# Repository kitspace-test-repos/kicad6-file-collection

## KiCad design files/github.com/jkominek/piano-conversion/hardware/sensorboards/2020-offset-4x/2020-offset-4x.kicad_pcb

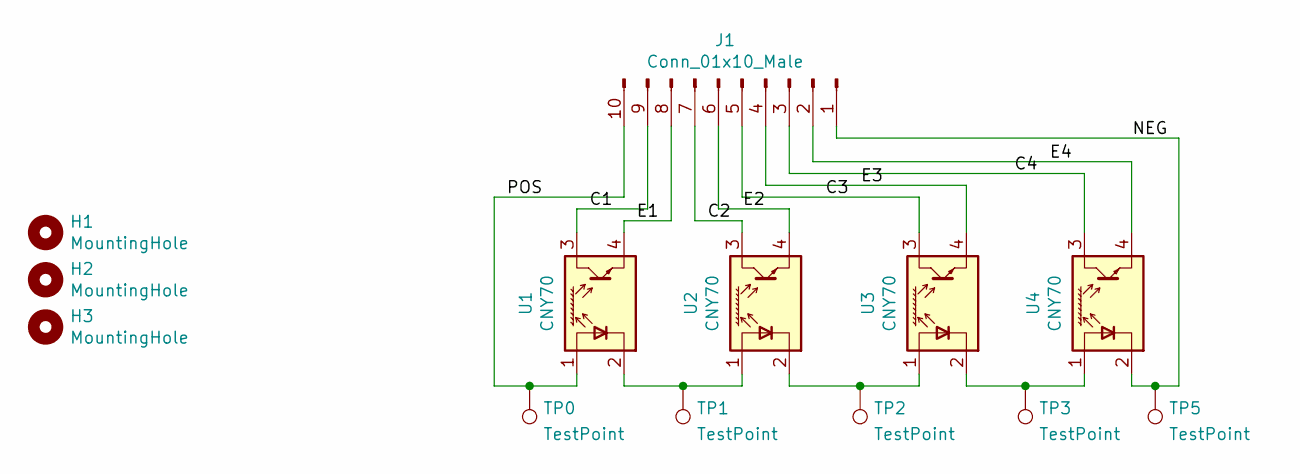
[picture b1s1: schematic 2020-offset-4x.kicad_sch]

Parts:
H1, H2, H3: MountingHole; MountingHole_3.2mm_M3
J1: Conn_01x10_Male; Pin_Header_Angled_1x10_Pitch2.54mm
TP0, TP1, TP2, TP3, TP5: TestPoint; TestPoint_Pad_1.0x1.0mm
U1, U2, U3, U4: CNY70; Vishay_CNY70

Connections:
/C1: J1.9, U1.3 (C)
/C2: J1.7, U2.3 (C)
/C3: J1.5, U3.3 (C)
/C4: J1.3, U4.3 (C)
/E1: J1.8, U1.4 (E)
/E2: J1.6, U2.4 (E)
/E3: J1.4, U3.4 (E)
/E4: J1.2, U4.4 (E)
/NEG: J1.1, TP5.1, U4.2 (K)
/POS: J1.10, TP0.1, U1.1 (A)
unnamed: TP1.1, U1.2 (K), U2.1 (A)
unnamed: TP2.1, U2.2 (K), U3.1 (A)
unnamed: TP3.1, U3.2 (K), U4.1 (A)

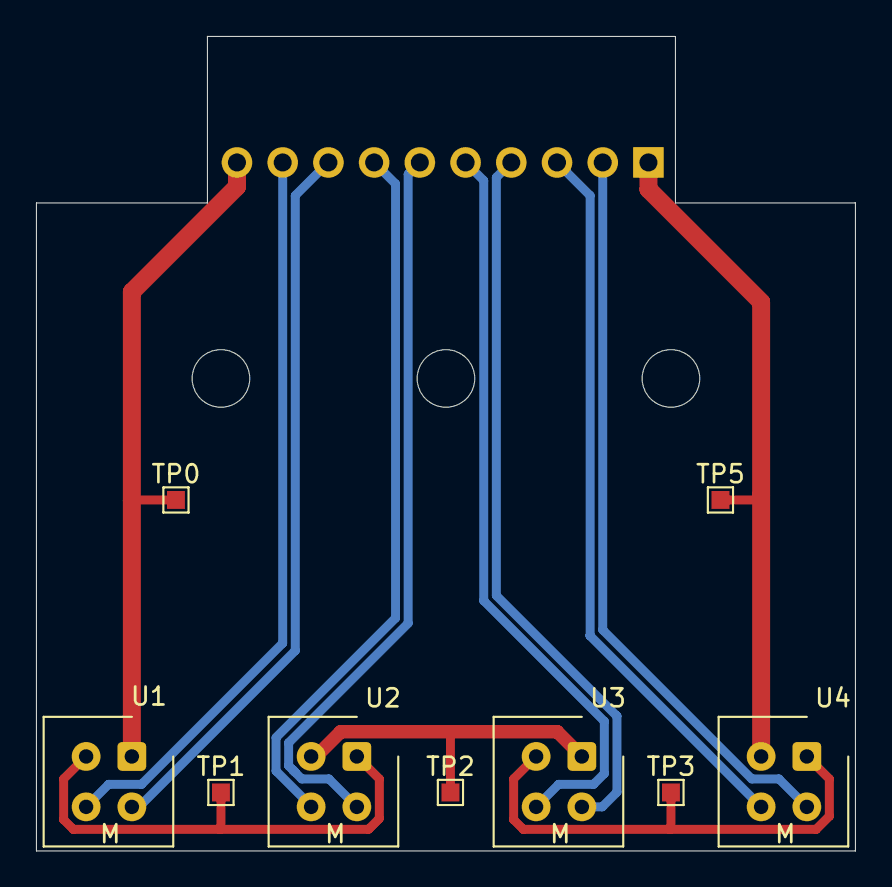
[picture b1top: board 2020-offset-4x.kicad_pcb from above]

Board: 2 copper layers, 45.5 x 45.2 mm, 13 parts (1 on the bottom side), 13 nets.

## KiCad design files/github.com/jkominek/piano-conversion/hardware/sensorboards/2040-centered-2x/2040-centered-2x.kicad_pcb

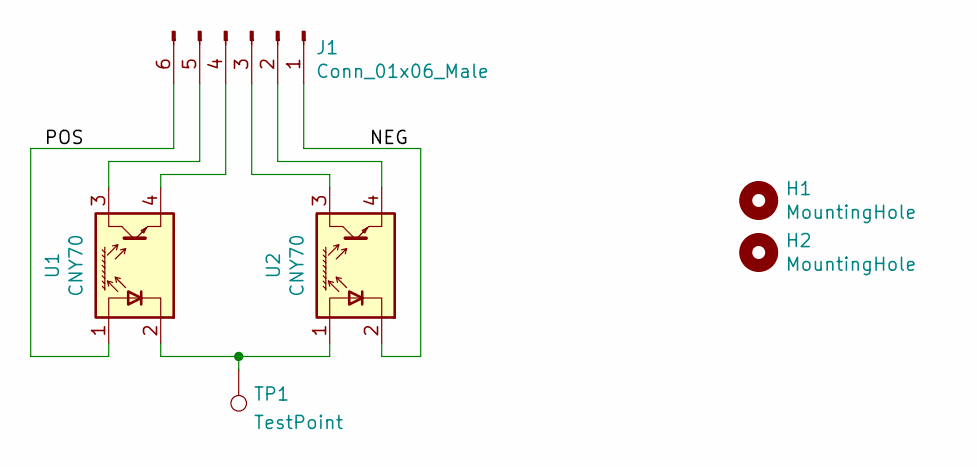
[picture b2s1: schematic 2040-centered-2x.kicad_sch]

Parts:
H1, H2: MountingHole; MountingHole_3.2mm_M3
J1: Conn_01x06_Male; Pin_Header_Angled_1x06_Pitch2.54mm
TP1: TestPoint; TestPoint_Pad_1.0x1.0mm
U1, U2: CNY70; Vishay_CNY70

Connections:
/NEG: J1.1, U2.2 (K)
/POS: J1.6, U1.1 (A)
unnamed: J1.2, U2.4 (E)
unnamed: J1.3, U2.3 (C)
unnamed: J1.4, U1.4 (E)
unnamed: J1.5, U1.3 (C)
unnamed: TP1.1, U1.2 (K), U2.1 (A)

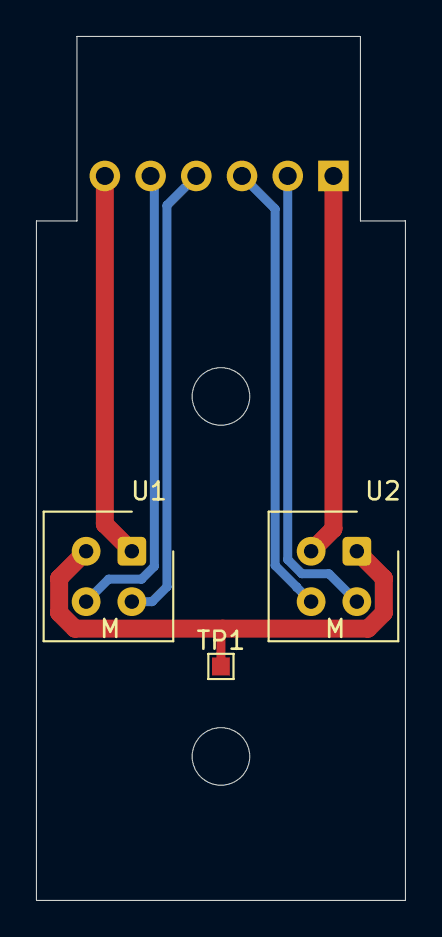
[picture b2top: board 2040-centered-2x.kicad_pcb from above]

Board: 2 copper layers, 20.5 x 48.0 mm, 6 parts (1 on the bottom side), 7 nets.

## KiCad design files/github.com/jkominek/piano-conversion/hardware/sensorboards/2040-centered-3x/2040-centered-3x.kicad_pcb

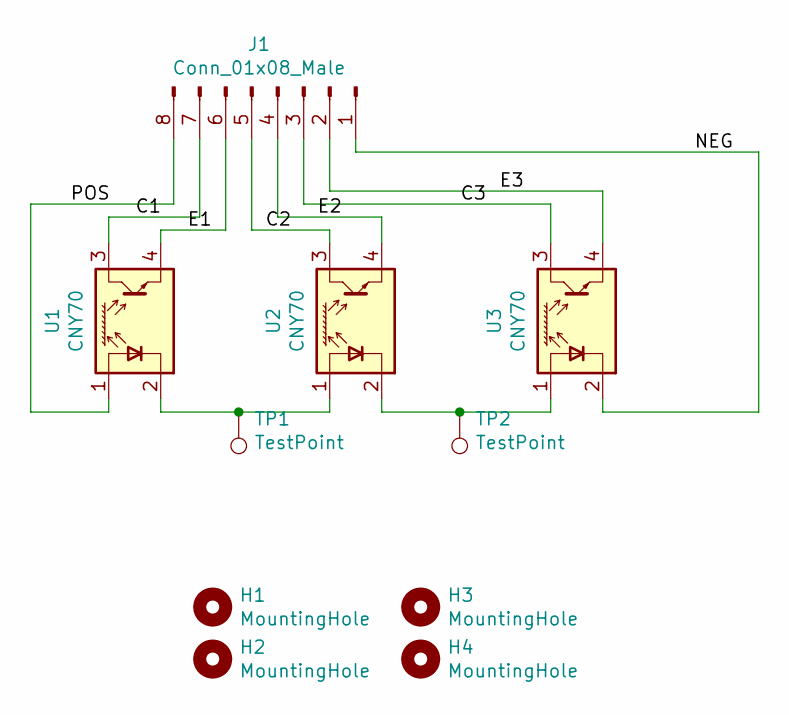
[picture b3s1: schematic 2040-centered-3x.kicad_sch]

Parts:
H1, H2, H3, H4: MountingHole; MountingHole_3.2mm_M3
J1: Conn_01x08_Male; PinHeader_1x08_P2.54mm_Horizontal
TP1, TP2: TestPoint; TestPoint_Pad_1.0x1.0mm
U1, U2, U3: CNY70; Vishay_CNY70

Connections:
/C1: J1.7, U1.3 (C)
/C2: J1.5, U2.3 (C)
/C3: J1.3, U3.3 (C)
/E1: J1.6, U1.4 (E)
/E2: J1.4, U2.4 (E)
/E3: J1.2, U3.4 (E)
/NEG: J1.1, U3.2 (K)
/POS: J1.8, U1.1 (A)
unnamed: TP1.1, U1.2 (K), U2.1 (A)
unnamed: TP2.1, U2.2 (K), U3.1 (A)

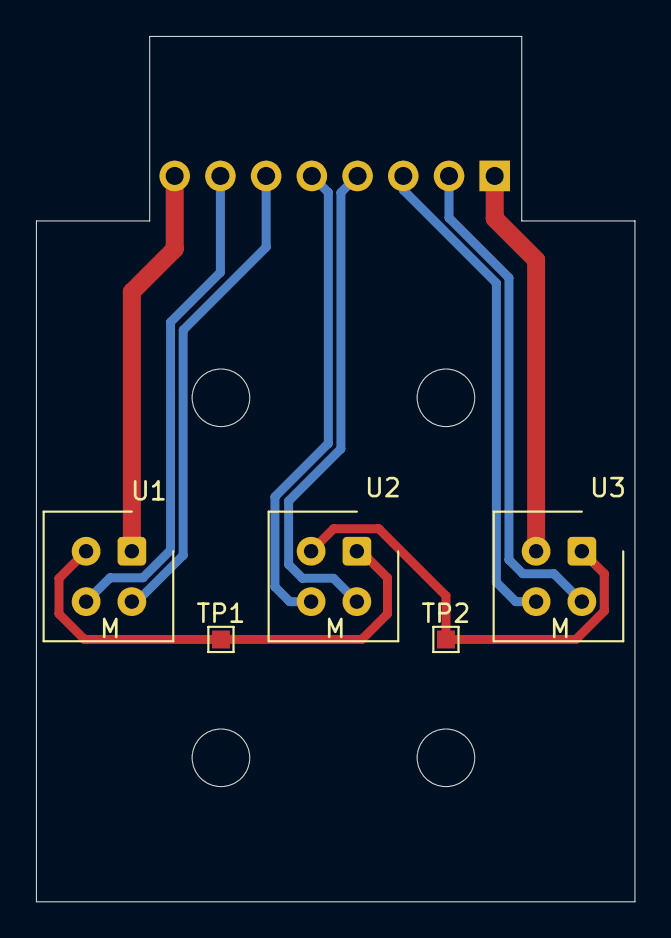
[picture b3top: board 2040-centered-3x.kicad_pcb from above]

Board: 2 copper layers, 33.2 x 48.1 mm, 10 parts (1 on the bottom side), 10 nets.

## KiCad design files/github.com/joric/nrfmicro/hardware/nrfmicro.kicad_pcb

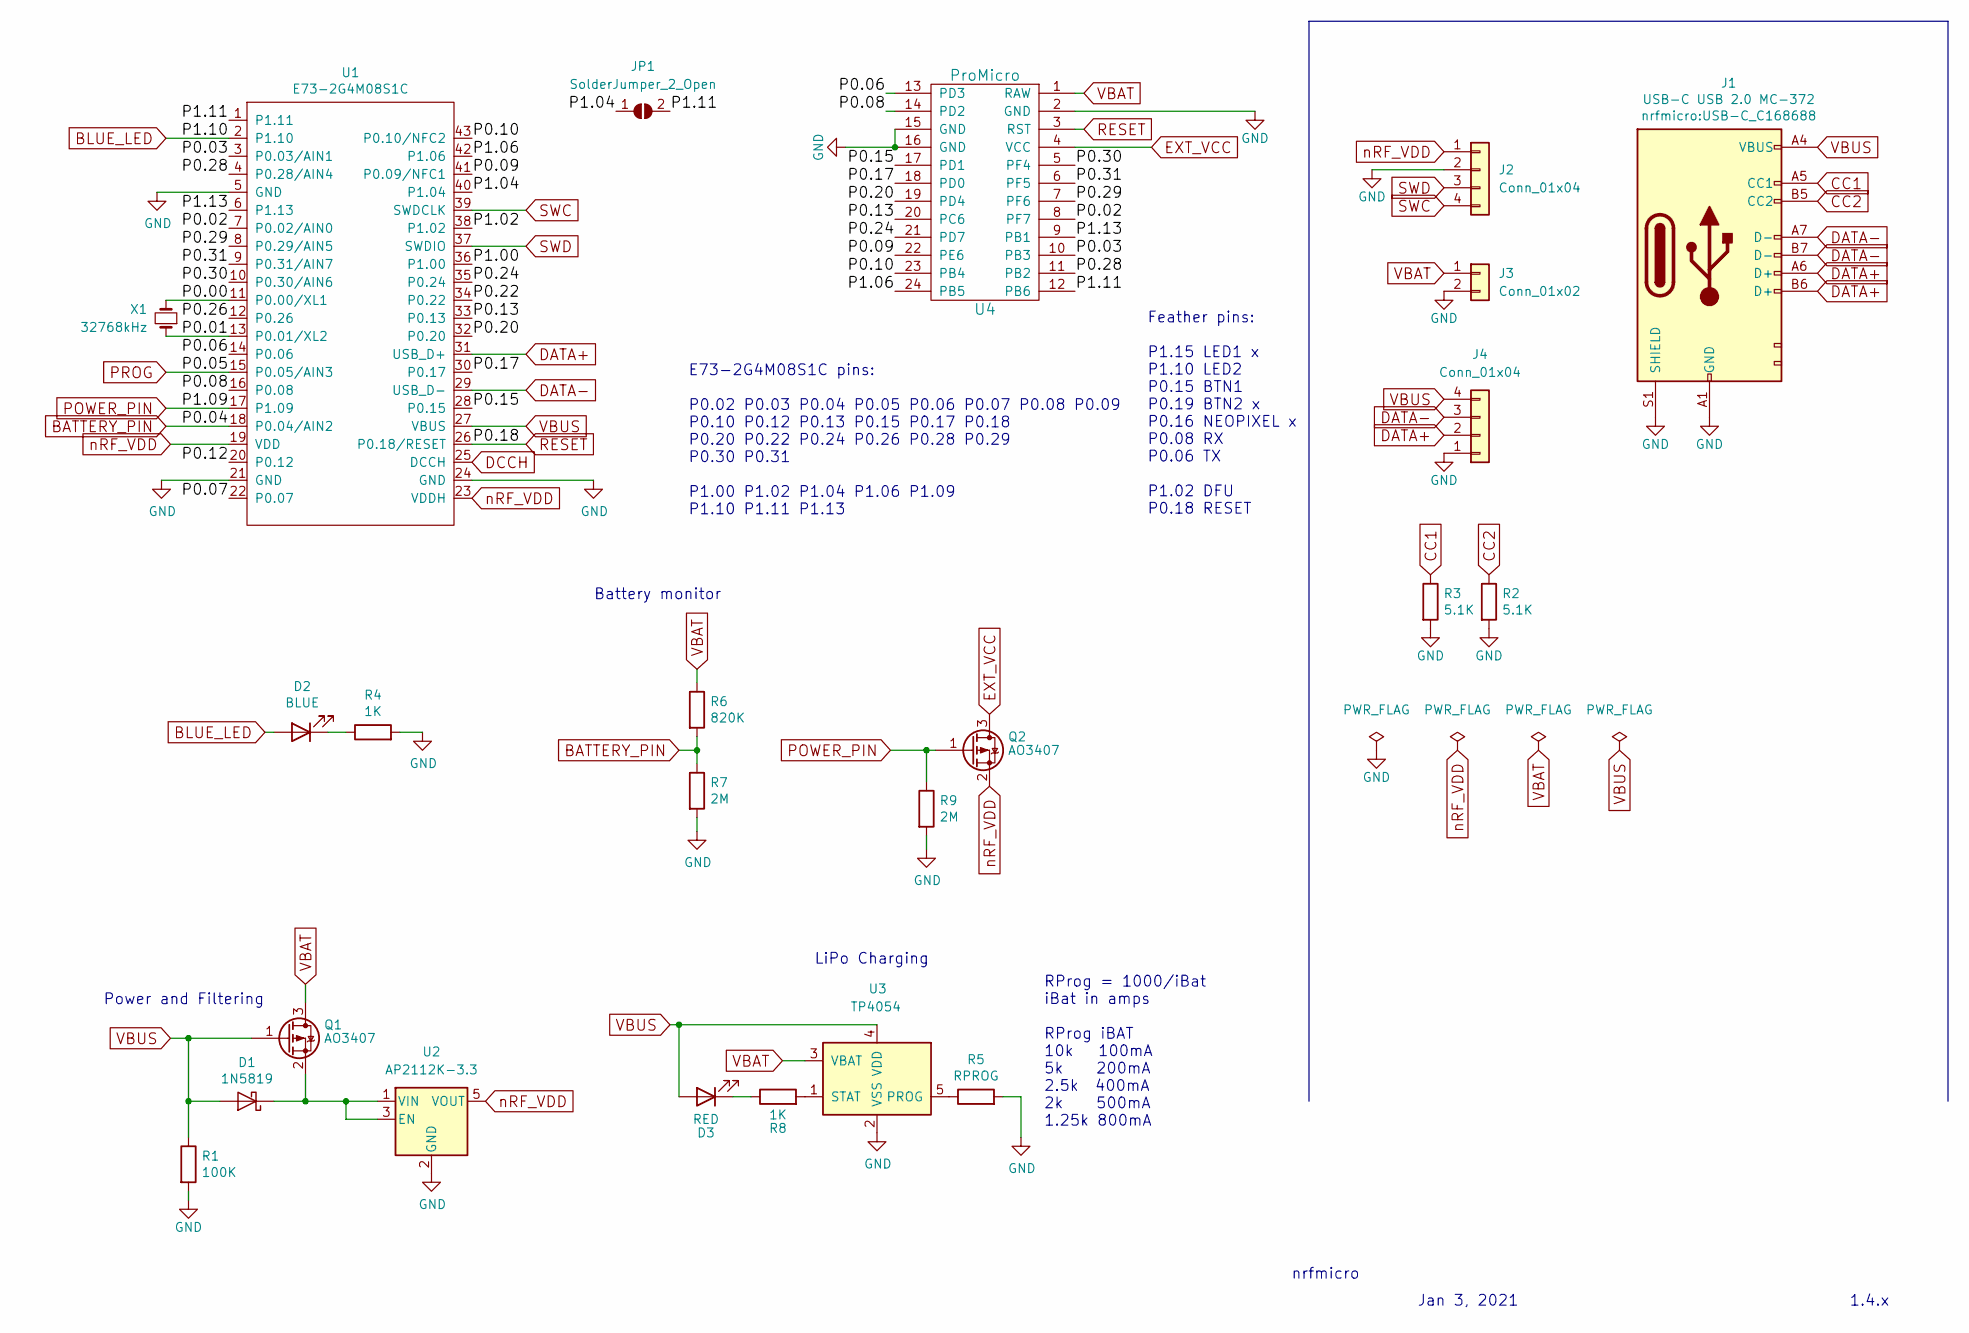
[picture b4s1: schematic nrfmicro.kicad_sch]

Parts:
D1: 1N5819; D_SOD-323F
D2: BLUE; LED_0603_1608Metric
D3: RED; LED_0603_1608Metric
J1: USB-C USB 2.0 MC-372; USB-C_C168688
J2: Conn_01x04; connector_swd
J3: Conn_01x02
J4: Conn_01x04; connector_usb
JP1: SolderJumper_2_Open; Jumper_SMD
Q1, Q2: AO3407; SOT-23
R1: 100K; R_0603_1608Metric
R2, R3: 5.1K; R_0603_1608Metric
R4, R8: 1K; R_0603_1608Metric
R5: RPROG; R_0603_1608Metric
R6: 820K; R_0603_1608Metric
R7, R9: 2M; R_0603_1608Metric
U1: E73-2G4M08S1C; E73-2G4M08S1C-52840
U2: AP2112K-3.3; SOT-23-5
U3: TP4054; SOT-23-5
U4: ProMicro; pro_micro
X1: 32768kHz

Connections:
/P0.00: U1.11 (P0.00/XL1), X1.2
/P0.01: U1.13 (P0.01/XL2), X1.1
/P0.02: U1.7 (P0.02/AIN0), U4.8 (PF7)
/P0.03: U1.3 (P0.03/AIN1), U4.10 (PB3)
/P0.06: U1.14 (P0.06), U4.13 (PD3)
/P0.07: U1.22 (P0.07)
/P0.08: U1.16 (P0.08), U4.14 (PD2)
/P0.09: U1.41 (P0.09/NFC1), U4.22 (PE6)
/P0.10: U1.43 (P0.10/NFC2), U4.23 (PB4)
/P0.12: U1.20 (P0.12)
/P0.13: U1.33 (P0.13), U4.20 (PC6)
/P0.15: U1.28 (P0.15), U4.17 (PD1)
/P0.17: U1.30 (P0.17), U4.18 (PD0)
/P0.20: U1.32 (P0.20), U4.19 (PD4)
/P0.22: U1.34 (P0.22)
/P0.24: U1.35 (P0.24), U4.21 (PD7)
/P0.26: U1.12 (P0.26)
/P0.28: U1.4 (P0.28/AIN4), U4.11 (PB2)
/P0.29: U1.8 (P0.29/AIN5), U4.7 (PF6)
/P0.30: U1.10 (P0.30/AIN6), U4.5 (PF4)
/P0.31: U1.9 (P0.31/AIN7), U4.6 (PF5)
/P1.00: U1.36 (P1.00)
/P1.02: U1.38 (P1.02)
/P1.04: JP1.1 (A), U1.40 (P1.04)
/P1.06: U1.42 (P1.06), U4.24 (PB5)
/P1.11: JP1.2 (B), U1.1 (P1.11), U4.12 (PB6)
/P1.13: U1.6 (P1.13), U4.9 (PB1)
BATTERY_PIN: R6.2, R7.1, U1.18 (P0.04/AIN2)
BLUE_LED: D2.2 (A), U1.2 (P1.10)
CC1: J1.A5 (CC1), R3.1
CC2: J1.B5 (CC2), R2.1
DATA+: J1.A6 (D+), J1.B6 (D+), J4.2, U1.31 (USB_D+)
DATA-: J1.A7 (D-), J1.B7 (D-), J4.3, U1.29 (USB_D-)
DCCH: U1.25 (DCCH)
EXT_VCC: Q2.3 (D), U4.4 (VCC)
GND: J1.A1 (GND), J1.S1 (SHIELD), J2.2, J3.2, J4.1, R1.2, R2.2, R3.2, R4.2, R5.2, R7.2, R9.2, U1.5 (GND), U1.21 (GND), U1.24 (GND), U2.2 (GND), U3.2 (VSS), U4.2 (GND), U4.15 (GND), U4.16 (GND)
unnamed: D1.1 (K), Q1.2 (S), U2.1 (VIN), U2.3 (EN)
unnamed: D2.1 (K), R4.1
unnamed: D3.1 (K), R8.1
unnamed: R5.1, U3.5 (PROG)
unnamed: R8.2, U3.1 (STAT)
POWER_PIN: Q2.1 (G), R9.1, U1.17 (P1.09)
PROG: U1.15 (P0.05/AIN3)
RESET: U1.26 (P0.18/RESET), U4.3 (RST)
SWC: J2.4, U1.39 (SWDCLK)
SWD: J2.3, U1.37 (SWDIO)
VBAT: J3.1, Q1.3 (D), R6.1, U3.3 (VBAT), U4.1 (RAW)
VBUS: D1.2 (A), D3.2 (A), J1.A4 (VBUS), J4.4, Q1.1 (G), R1.1, U1.27 (VBUS), U3.4 (VDD)
nRF_VDD: J2.1, Q2.2 (S), U1.19 (VDD), U1.23 (VDDH), U2.5 (VOUT)

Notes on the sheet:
LiPo Charging
Jan 3, 2021
1.4.x
RProg = 1000/iBat iBat in amps RProg iBAT 10k 100mA 5k 200mA 2.5k 400mA 2k 500mA 1.25k 800mA
Power and Filtering
nrfmicro
Battery monitor
E73-2G4M08S1C pins: P0.02 P0.03 P0.04 P0.05 P0.06 P0.07 P0.08 P0.09 P0.10 P0.12 P0.13 P0.15 P0.17 P0.18 P0.20 P0.22 P0.24 P0.26 P0.28 P0.29 P0.30 P0.31 P1.00 P1.02 P1.04 P1.06 P1.09 P1.10 P1.11 P1.13
Feather pins: P1.15 LED1 x P1.10 LED2 P0.15 BTN1 P0.19 BTN2 x P0.16 NEOPIXEL x P0.08 RX P0.06 TX P1.02 DFU P0.18 RESET

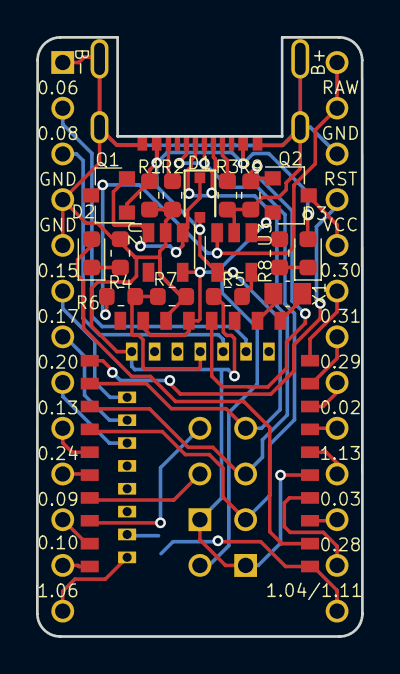
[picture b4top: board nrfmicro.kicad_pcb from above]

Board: 2 copper layers, 18.1 x 33.3 mm, 24 parts (1 on the bottom side), 41 nets.

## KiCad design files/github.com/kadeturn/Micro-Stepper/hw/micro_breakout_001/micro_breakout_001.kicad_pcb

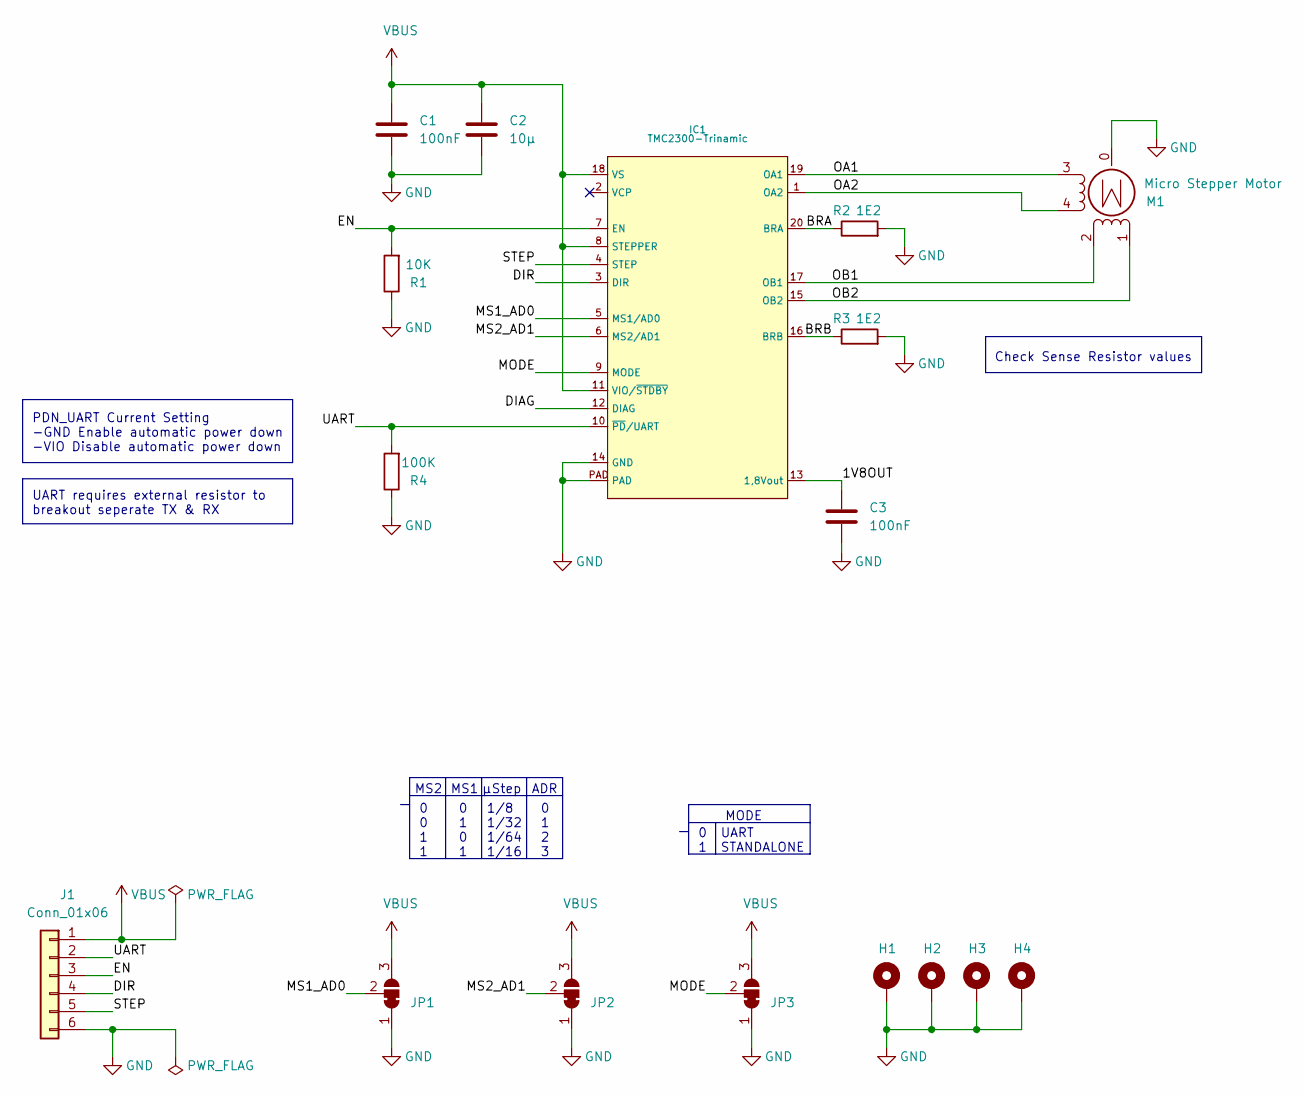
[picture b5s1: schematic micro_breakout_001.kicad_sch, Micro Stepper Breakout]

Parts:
C1, C3: 100nF; C_0402_1005Metric
C2: 10µ; C_0603_1608Metric
H1, H2, H3, H4: MountingHole; Mounting_Wuerth_WA-SMSI-M1.6_H1mm_9774010633
IC1: TMC2300-Trinamic; QFN20
J1: Conn_01x06; JST_SH_SM06B-SRSS-TB_1x06-1MP_P1.00mm_Horizontal
JP1, JP2, JP3: SolderJumper_3_Bridged12; J_NCNO_0903_20
M1: Micro Stepper Motor; Micro_Stepper
R1: 10K; R_0402_1005Metric
R2, R3: 1E2; R_0402_1005Metric
R4: 100K; R_0402_1005Metric

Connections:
/1V8OUT: C3.1, IC1.13 (1,8Vout)
/BRA: IC1.20 (BRA), R2.1
/BRB: IC1.16 (BRB), R3.1
/DIAG: IC1.12 (DIAG)
/DIR: IC1.3 (DIR), J1.4
/EN: IC1.7 (EN), J1.3, R1.2
/MODE: IC1.9 (MODE), JP3.2 (C)
/MS1_AD0: IC1.5 (MS1/AD0), JP1.2 (C)
/MS2_AD1: IC1.6 (MS2/AD1), JP2.2 (C)
/OA1: IC1.19 (OA1), M1.3
/OA2: IC1.1 (OA2), M1.4
/OB1: IC1.17 (OB1), M1.2 (-)
/OB2: IC1.15 (OB2), M1.1
/STEP: IC1.4 (STEP), J1.5
/UART: IC1.10 (~PD~/UART), J1.2, R4.2
GND: C1.2, C2.2, C3.2, H1.1, H2.1, H3.1, H4.1, IC1.14 (GND), IC1.PAD, J1.6, JP1.1 (A), JP2.1 (A), JP3.1 (A), M1.0 (Sheild), R1.1, R2.2, R3.2, R4.1
VBUS: C1.1, C2.1, IC1.8 (STEPPER), IC1.11 (VIO/~STDBY), IC1.18 (VS), J1.1, JP1.3 (B), JP2.3 (B), JP3.3 (B)

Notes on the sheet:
PDN_UART Current Setting -GND Enable automatic power down -VIO Disable automatic power down
UART requires external resistor to breakout seperate TX & RX
MS2
0 0 1 1
MS1
0 1 0 1
µStep
1/8 1/32 1/64 1/16
ADR
0 1 2 3
0 1
UART STANDALONE
MODE
Check Sense Resistor values

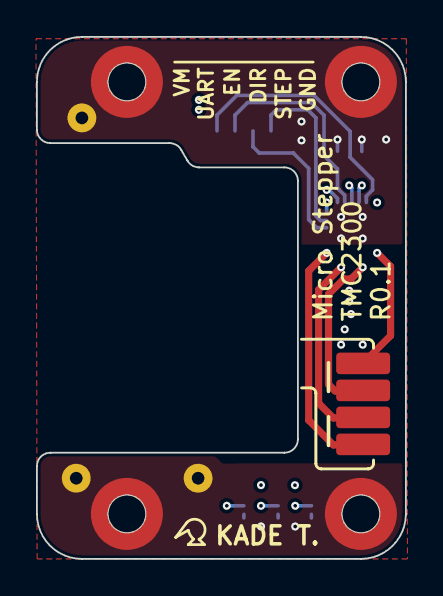
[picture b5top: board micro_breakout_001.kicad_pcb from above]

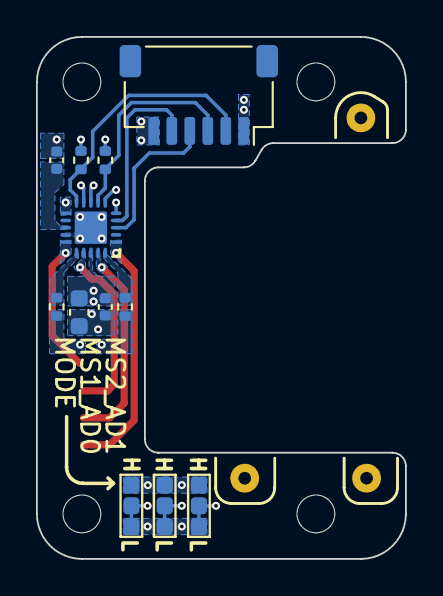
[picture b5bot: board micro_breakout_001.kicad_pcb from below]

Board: 4 copper layers, 20.5 x 29.0 mm, 17 parts (13 on the bottom side), 16 nets.

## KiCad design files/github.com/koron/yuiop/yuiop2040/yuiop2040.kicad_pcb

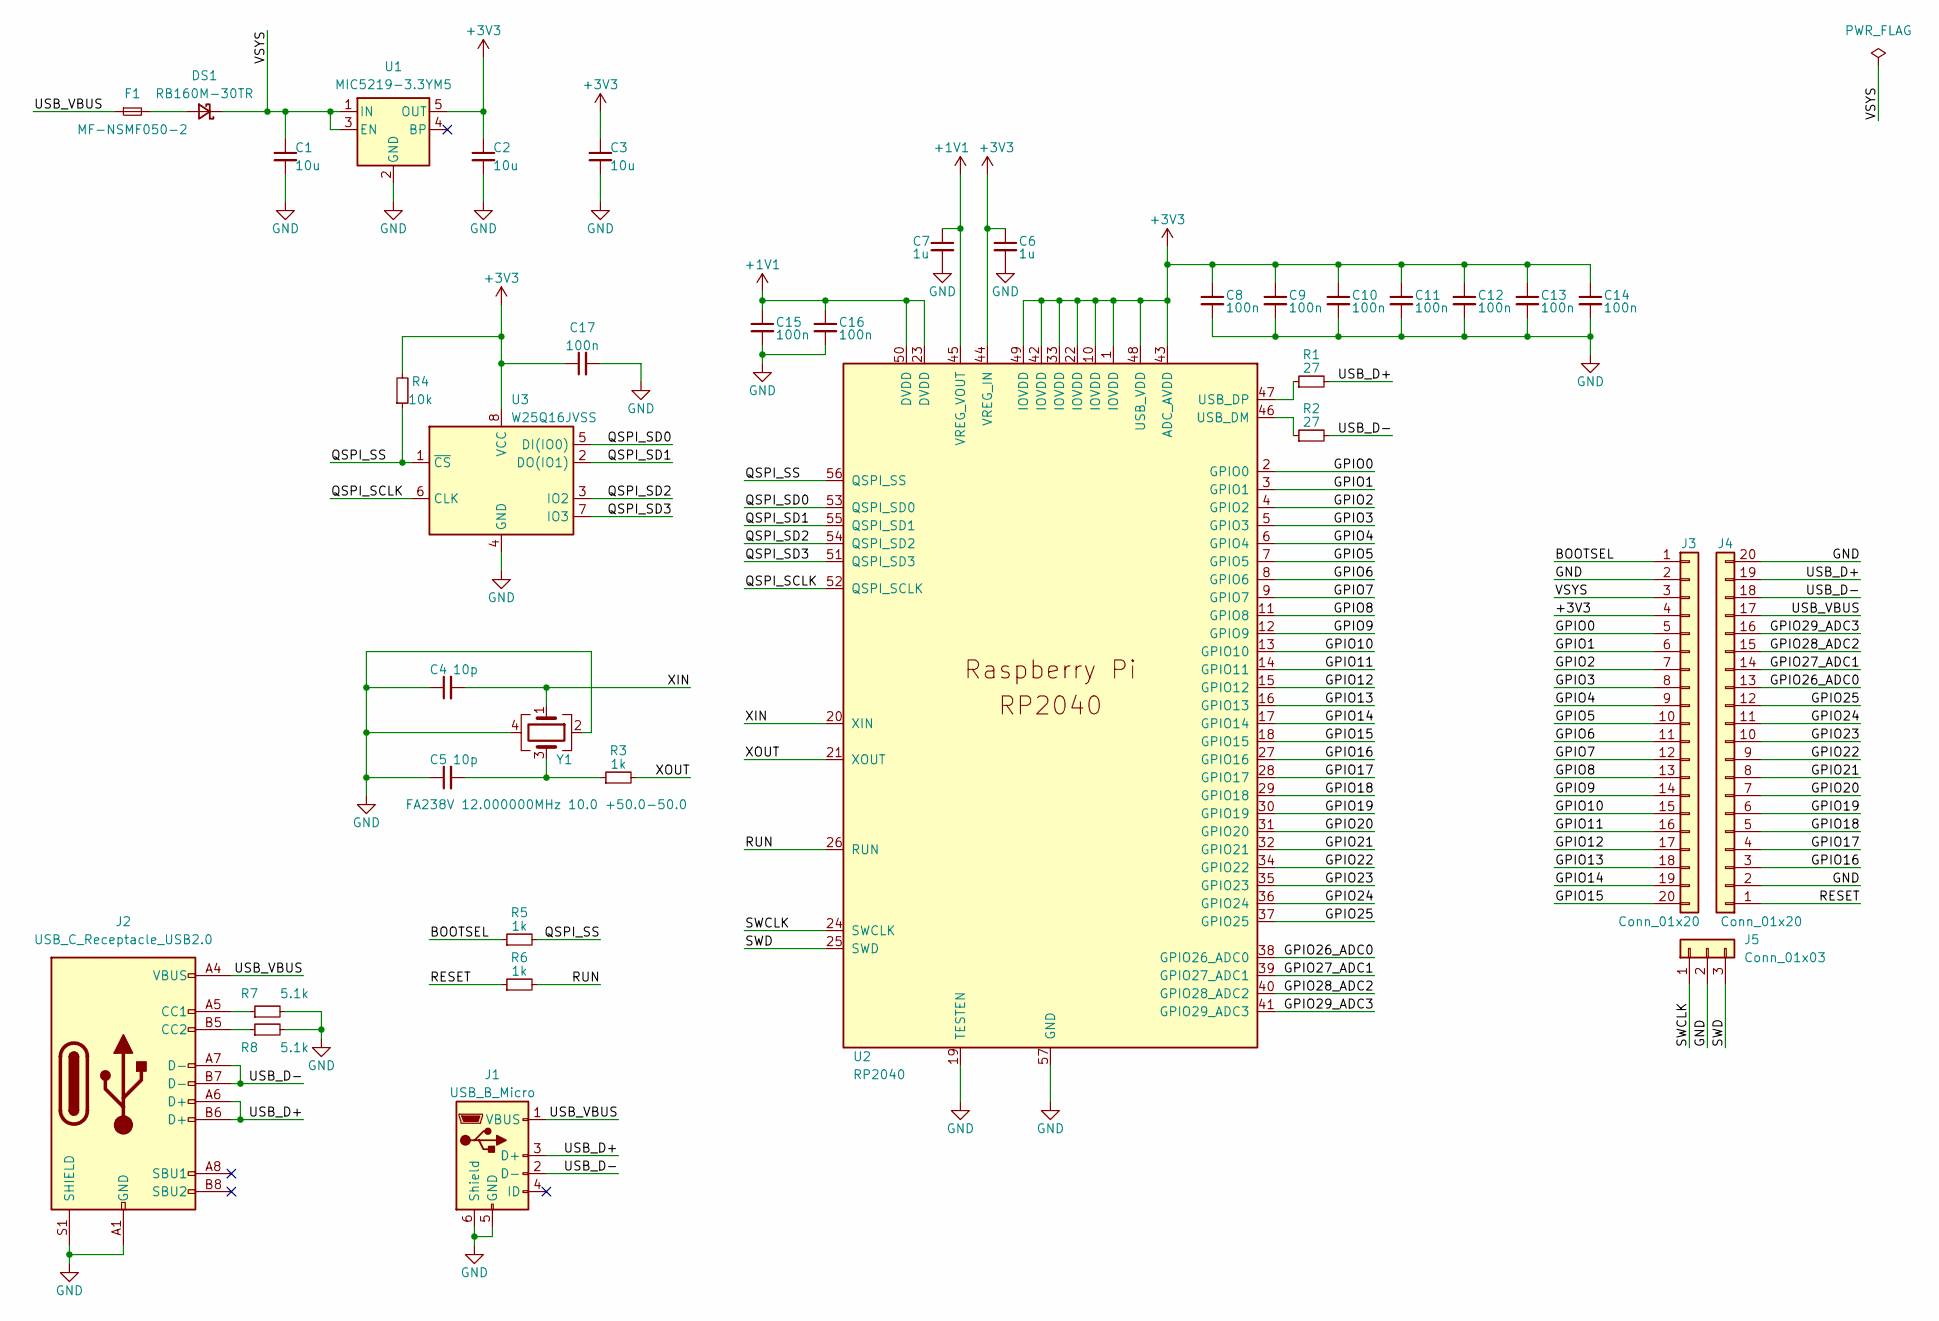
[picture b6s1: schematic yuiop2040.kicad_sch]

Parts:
C1, C2, C3: 10u; C_0603_1608Metric
C4, C5: 10p; C_0603_1608Metric
C6, C7: 1u; C_0603_1608Metric
C8, C9, C10, C11, C12, C13, C14, C15, C16, C17: 100n; C_0603_1608Metric
DS1: RB160M-30TR; D_SOD-123
F1: MF-NSMF050-2; Fuse_1206_3216Metric
J1: USB_B_Micro; USB_Micro-B_Amphenol_10103594-0001LF_Horizontal
J2: USB_C_Receptacle_USB2.0; USB_C_Receptacle_XKB_U262-16XN-4BVC11
J3, J4: Conn_01x20; PinHeader_1x20_P2.54mm_Vertical
J5: Conn_01x03; PinHeader_1x03_P2.54mm_Vertical
R1, R2: 27; R_0603_1608Metric
R3, R5, R6: 1k; R_0603_1608Metric
R4: 10k; R_0603_1608Metric
R7, R8: 5.1k; R_0603_1608Metric
U1: MIC5219-3.3YM5; SOT-23-5
U2: RP2040; RP2040-QFN-56-r2
U3: W25Q16JVSS; SOIC-8_3.9x4.9mm_P1.27mm
Y1: FA238V 12.000000MHz 10.0 +50.0-50.0; Crystal_SMD_SeikoEpson_FA238V-4Pin_3.2x2.5mm

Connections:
+1V1: C7.1, C15.1, C16.1, U2.23 (DVDD), U2.45 (VREG_VOUT), U2.50 (DVDD)
+3V3: C2.1, C3.1, C6.1, C8.1, C9.1, C10.1, C11.1, C12.1, C13.1, C14.1, C17.1, J3.4, R4.2, U1.5 (OUT), U2.1 (IOVDD), U2.10 (IOVDD), U2.22 (IOVDD), U2.33 (IOVDD), U2.42 (IOVDD), U2.43 (ADC_AVDD), U2.44 (VREG_IN), U2.48 (USB_VDD), U2.49 (IOVDD), U3.8 (VCC)
/BOOTSEL: J3.1, R5.1
/GPIO0: J3.5, U2.2 (GPIO0)
/GPIO1: J3.6, U2.3 (GPIO1)
/GPIO2: J3.7, U2.4 (GPIO2)
/GPIO3: J3.8, U2.5 (GPIO3)
/GPIO4: J3.9, U2.6 (GPIO4)
/GPIO5: J3.10, U2.7 (GPIO5)
/GPIO6: J3.11, U2.8 (GPIO6)
/GPIO7: J3.12, U2.9 (GPIO7)
/GPIO8: J3.13, U2.11 (GPIO8)
/GPIO9: J3.14, U2.12 (GPIO9)
/GPIO10: J3.15, U2.13 (GPIO10)
/GPIO11: J3.16, U2.14 (GPIO11)
/GPIO12: J3.17, U2.15 (GPIO12)
/GPIO13: J3.18, U2.16 (GPIO13)
/GPIO14: J3.19, U2.17 (GPIO14)
/GPIO15: J3.20, U2.18 (GPIO15)
/GPIO16: J4.3, U2.27 (GPIO16)
/GPIO17: J4.4, U2.28 (GPIO17)
/GPIO18: J4.5, U2.29 (GPIO18)
/GPIO19: J4.6, U2.30 (GPIO19)
/GPIO20: J4.7, U2.31 (GPIO20)
/GPIO21: J4.8, U2.32 (GPIO21)
/GPIO22: J4.9, U2.34 (GPIO22)
/GPIO23: J4.10, U2.35 (GPIO23)
/GPIO24: J4.11, U2.36 (GPIO24)
/GPIO25: J4.12, U2.37 (GPIO25)
/GPIO26_ADC0: J4.13, U2.38 (GPIO26_ADC0)
/GPIO27_ADC1: J4.14, U2.39 (GPIO27_ADC1)
/GPIO28_ADC2: J4.15, U2.40 (GPIO28_ADC2)
/GPIO29_ADC3: J4.16, U2.41 (GPIO29_ADC3)
/QSPI_SCLK: U2.52 (QSPI_SCLK), U3.6 (CLK)
/QSPI_SD0: U2.53 (QSPI_SD0), U3.5 (DI(IO0))
/QSPI_SD1: U2.55 (QSPI_SD1), U3.2 (DO(IO1))
/QSPI_SD2: U2.54 (QSPI_SD2), U3.3 (IO2)
/QSPI_SD3: U2.51 (QSPI_SD3), U3.7 (IO3)
/QSPI_SS: R4.1, R5.2, U2.56 (QSPI_SS), U3.1 (~CS)
/RESET: J4.1, R6.1
/RUN: R6.2, U2.26 (RUN)
/SWCLK: J5.1, U2.24 (SWCLK)
/SWD: J5.3, U2.25 (SWD)
/USB_D+: J1.3 (D+), J2.A6 (D+), J2.B6 (D+), J4.19, R1.2
/USB_D-: J1.2 (D-), J2.A7 (D-), J2.B7 (D-), J4.18, R2.2
/USB_VBUS: F1.1, J1.1 (VBUS), J2.A4 (VBUS), J2.A9 (VBUS), J2.B4 (VBUS), J2.B9 (VBUS), J4.17
/VSYS: C1.1, DS1.1 (K), J3.3, U1.1 (IN), U1.3 (EN)
/XIN: C4.2, U2.20 (XIN), Y1.1
/XOUT: R3.2, U2.21 (XOUT)
GND: C1.2, C2.2, C3.2, C4.1, C5.1, C6.2, C7.2, C8.2, C9.2, C10.2, C11.2, C12.2, C13.2, C14.2, C15.2, C16.2, C17.2, J1.5 (GND), J1.6 (Shield), J2.A1 (GND), J2.A12 (GND), J2.B1 (GND), J2.B12 (GND), J2.S1 (SHIELD), J3.2, J4.2, J4.20, J5.2, R7.2, R8.2, U1.2 (GND), U2.19 (TESTEN), U2.57 (GND), U3.4 (GND), Y1.2, Y1.4
unnamed: C5.2, R3.1, Y1.3
unnamed: DS1.2 (A), F1.2
unnamed: J2.A5 (CC1), R7.1
unnamed: J2.B5 (CC2), R8.1
unnamed: R1.1, U2.47 (USB_DP)
unnamed: R2.1, U2.46 (USB_DM)

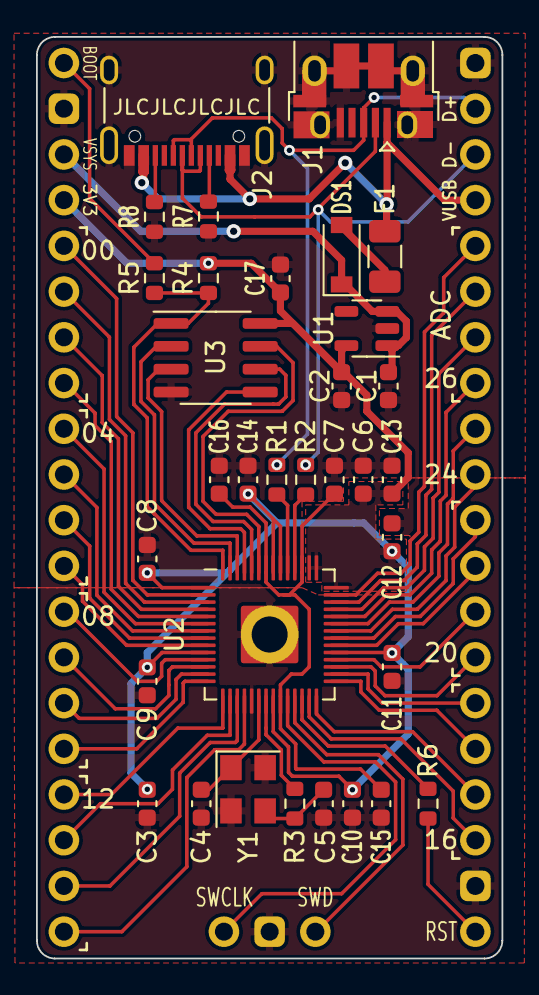
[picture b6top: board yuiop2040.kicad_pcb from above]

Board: 2 copper layers, 25.9 x 51.2 mm, 36 parts (0 on the bottom side), 56 nets.
